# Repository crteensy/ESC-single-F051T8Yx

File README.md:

# ESC-single-F051T8Yx
An ESC prototype based on the F051 in WLCSP-36, for AM32. NCP81253, SIZF360

Firmware: AM32, target doesn't exist yet.

## 3D Views
top  

bottom

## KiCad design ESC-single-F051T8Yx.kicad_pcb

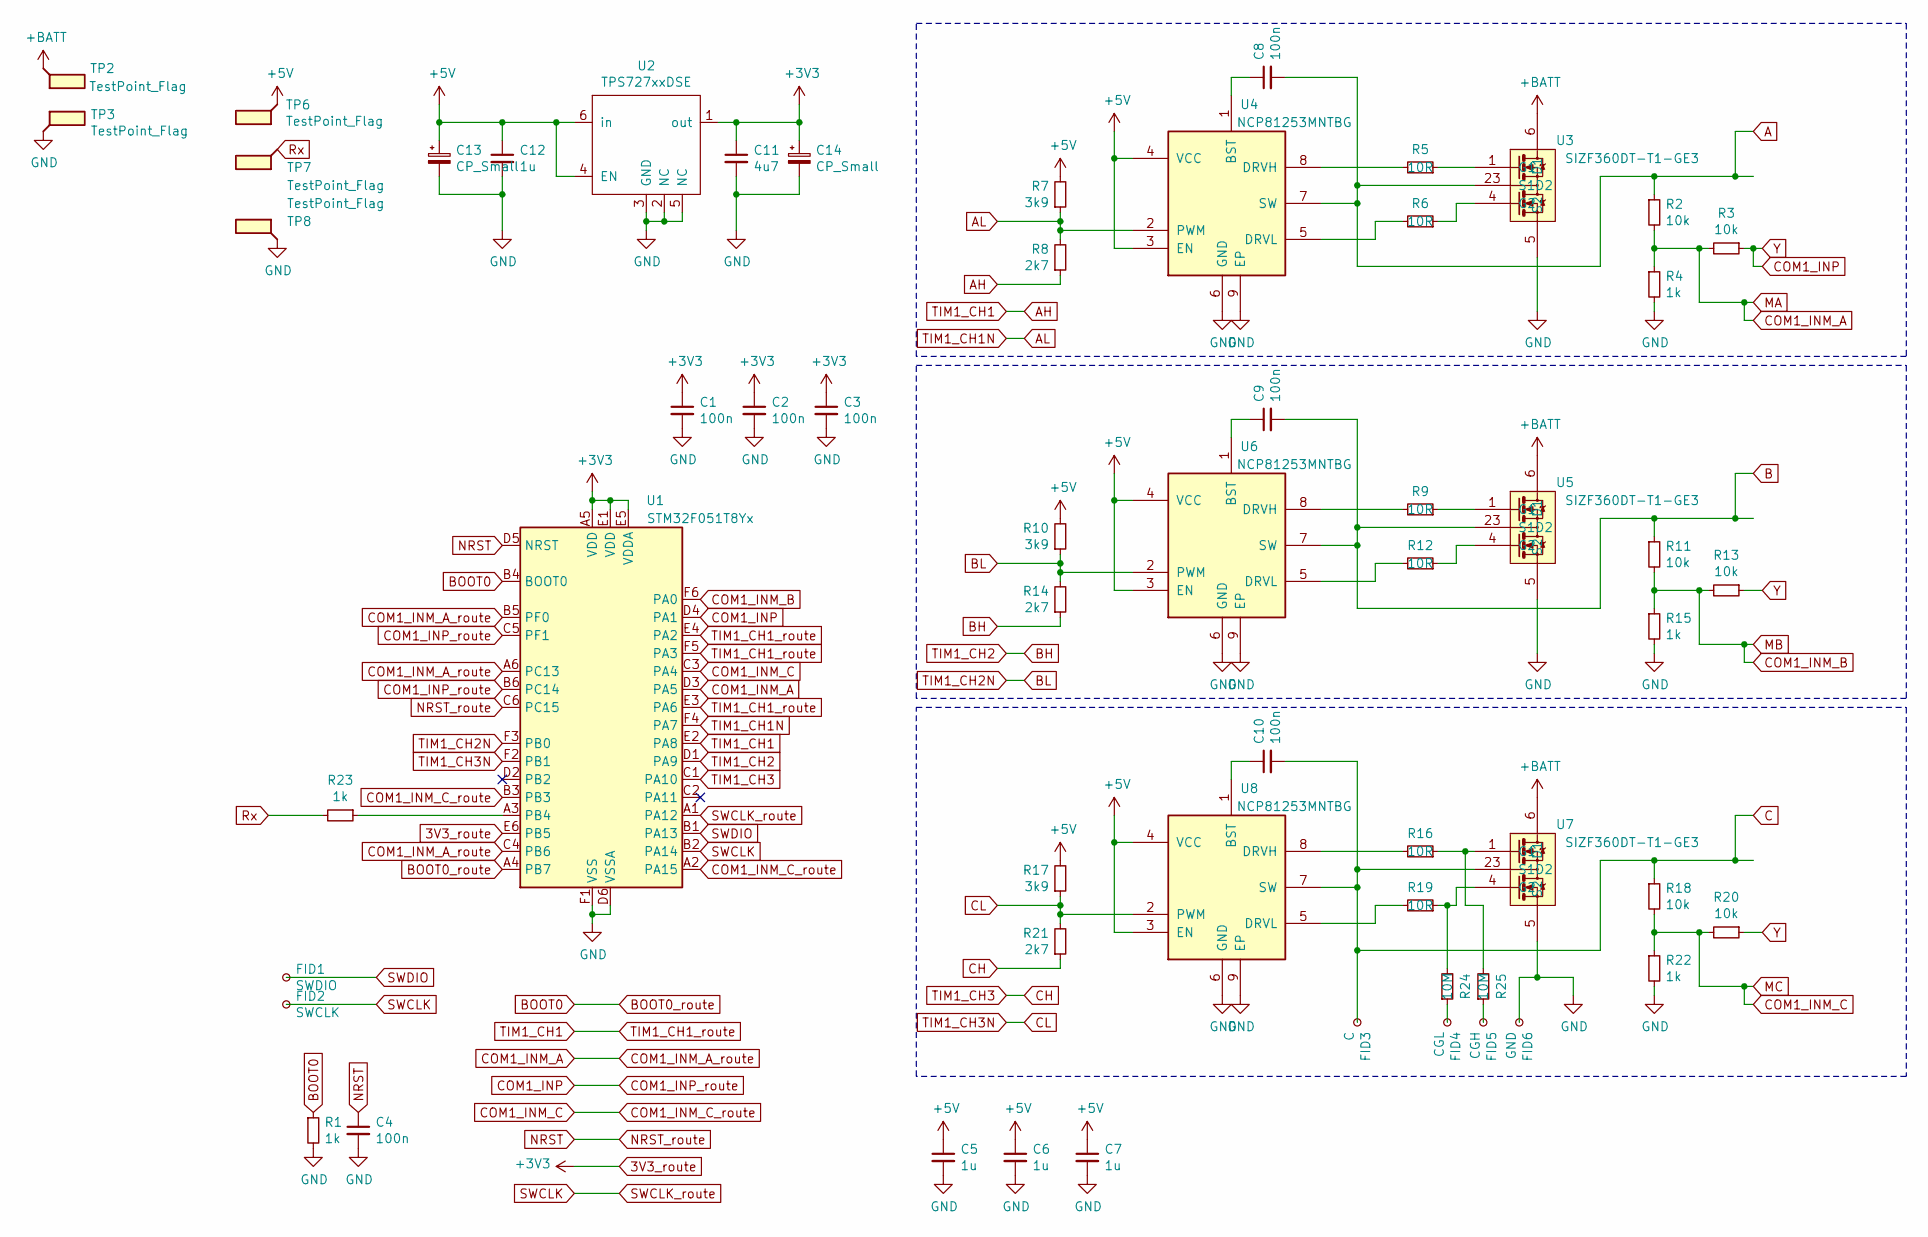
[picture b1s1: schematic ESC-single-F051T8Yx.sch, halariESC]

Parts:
C1, C2, C3, C4: 100n; C_0402_1005Metric
C5, C6, C7: 1u; C_0201_0603Metric
C8, C9, C10: 100n; C_0201_0603Metric
C11: 4u7; C_0402_1005Metric
C12: 1u; C_0402_1005Metric
C13, C14: CP_Small; CP_EIA-3528-12_Kemet-T
FID1: SWDIO; TestPoint_Pad_D1.0mm_dense
FID2: SWCLK; TestPoint_Pad_D1.0mm_dense
FID3: C; pad_io_1x1.5mm
FID4: CGL; pad_io_1x1.5mm
FID5: CGH; pad_io_1x1.5mm
FID6: GND; pad_io_1x1.5mm
R1, R23: 1k; R_0402_1005Metric
R2, R11, R18: 10k; R_0402_1005Metric
R3, R13, R20: 10k; R_0201_0603Metric_mod
R4, R15, R22: 1k; R_0201_0603Metric_mod
R5, R6, R9, R12, R16, R19: 10R; R_0201_0603Metric_mod
R7, R10, R17: 3k9; R_0201_0603Metric_mod
R8, R14, R21: 2k7; R_0201_0603Metric_mod
R24, R25: 10M; R_0402_1005Metric
TP2, TP3: TestPoint_Flag; TestPoint_Pad_2.5x2.5mm
TP6, TP7, TP8: TestPoint_Flag; pad_io_1x1.5mm
U1: STM32F051T8Yx; ST_WLCSP-36_Die440
U2: TPS727xxDSE; WSON-6_1.5x1.5mm_P0.5mm
U3, U5, U7: SIZF360DT-T1-GE3; PowerPair_3.3x3.3F_BWL_mod
U4, U6, U8: NCP81253MNTBG; DFN-8-1EP_2x2mm_P0.5mm_EP0.9x1.3mm_dense

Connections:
3V3_route: C1.1, C2.1, C3.1, C11.1, C14.1, U1.A5 (VDD), U1.E1 (VDD), U1.E5 (VDDA), U1.E6 (PB5), U2.1 (out)
+5V: C5.1, C6.1, C7.1, C12.1, C13.1, R7.2, R10.2, R17.2, TP6.1, U2.4 (EN), U2.6 (in), U4.3 (EN), U4.4 (VCC), U6.3 (EN), U6.4 (VCC), U8.3 (EN), U8.4 (VCC)
+BATT: TP2.1, U3.6 (D1), U5.6 (D1), U7.6 (D1)
A: C8.2, R2.1, U3.23 (S1D2), U4.7 (SW)
AH: R8.1, U1.E2 (PA8), U1.E3 (PA6), U1.E4 (PA2), U1.F5 (PA3)
AL: R7.1, R8.2, U1.F4 (PA7), U4.2 (PWM)
B: C9.2, R11.1, U5.23 (S1D2), U6.7 (SW)
BH: R14.1, U1.D1 (PA9)
BL: R10.1, R14.2, U1.F3 (PB0), U6.2 (PWM)
BOOT0: R1.1, U1.A4 (PB7), U1.B4 (BOOT0)
C: C10.2, FID3.1, R18.1, U7.23 (S1D2), U8.7 (SW)
CH: R21.1, U1.C1 (PA10)
CL: R17.1, R21.2, U1.F2 (PB1), U8.2 (PWM)
COM1_INM_A: R2.2, R3.2, R4.1, U1.A6 (PC13), U1.B5 (PF0), U1.C4 (PB6), U1.D3 (PA5)
COM1_INM_B: R11.2, R13.2, R15.1, U1.F6 (PA0)
COM1_INM_C: R18.2, R20.2, R22.1, U1.A2 (PA15), U1.B3, U1.C3 (PA4)
COM1_INP: R3.1, R13.1, R20.1, U1.B6 (PC14), U1.C5 (PF1), U1.D4 (PA1)
GND: C1.2, C2.2, C3.2, C4.2, C5.2, C6.2, C7.2, C11.2, C12.2, C13.2, C14.2, FID6.1, R1.2, R4.2, R15.2, R22.2, TP3.1, TP8.1, U1.D6 (VSSA), U1.F1 (VSS), U2.2 (NC), U2.3 (GND), U2.5 (NC), U3.5 (S2), U4.6 (GND), U4.9 (EP), U5.5 (S2), U6.6 (GND), U6.9 (EP), U7.5 (S2), U8.6 (GND), U8.9 (EP)
NRST: C4.1, U1.C6 (PC15), U1.D5 (NRST)
unnamed: C8.1, U4.1 (BST)
unnamed: C9.1, U6.1 (BST)
unnamed: C10.1, U8.1 (BST)
unnamed: FID4.1, R24.1
unnamed: FID5.1, R25.1
unnamed: R5.1, U3.1 (G1)
unnamed: R5.2, U4.8 (DRVH)
unnamed: R6.1, U3.4 (G2)
unnamed: R6.2, U4.5 (DRVL)
unnamed: R9.1, U5.1 (G1)
unnamed: R9.2, U6.8 (DRVH)
unnamed: R12.1, U5.4 (G2)
unnamed: R12.2, U6.5 (DRVL)
unnamed: R16.1, R25.2, U7.1 (G1)
unnamed: R16.2, U8.8 (DRVH)
unnamed: R19.1, R24.2, U7.4 (G2)
unnamed: R19.2, U8.5 (DRVL)
unnamed: R23.1, U1.A3 (PB4)
Rx: R23.2, TP7.1
SWCLK: FID2.1, U1.A1 (PA12), U1.B2 (PA14)
SWDIO: FID1.1, U1.B1 (PA13)

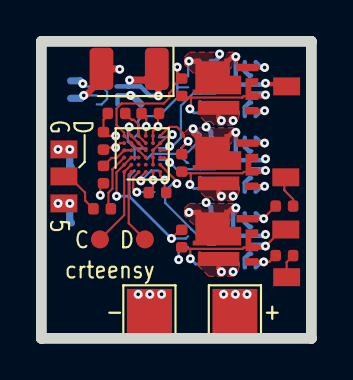
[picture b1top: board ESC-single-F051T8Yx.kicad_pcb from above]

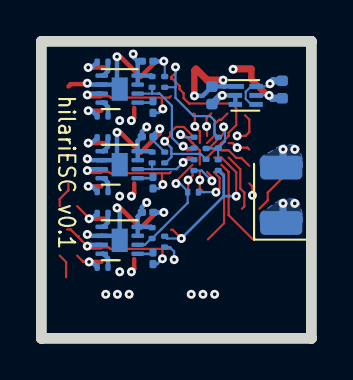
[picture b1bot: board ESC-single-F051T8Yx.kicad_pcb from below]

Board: 4 copper layers, 15.0 x 16.5 mm, 58 parts (31 on the bottom side), 40 nets.

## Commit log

2021-04-08 initial upload
2021-04-08 cleanup
2021-04-08 update SIZF360 footprint
2021-04-09 changed layout of gate masuring 10M resistors slightly
2021-04-09 update schematic, pdf, layout add 3d view PNGs
2021-04-09 update bottom silk screen
2021-04-10 overall update
2021-04-10 update bottom view
2021-04-11 update layout
